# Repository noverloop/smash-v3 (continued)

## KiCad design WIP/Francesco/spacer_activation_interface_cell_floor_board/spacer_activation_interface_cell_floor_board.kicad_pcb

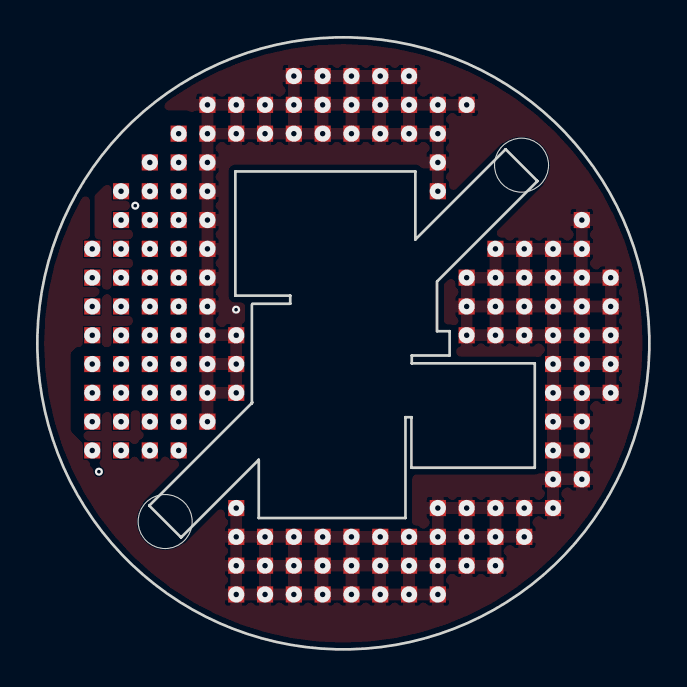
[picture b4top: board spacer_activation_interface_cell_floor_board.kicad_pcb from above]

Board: 4 copper layers, 34.0 x 34.0 mm, 4 parts (1 on the bottom side), 35 nets, no tracks yet.

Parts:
J_spacer_activation_interface_cell_floor_board_top: LGA_lands; J_spacer_activation_interface_cell_floor_board_top
MECH1, MECH2: smash_mech_potting
P_spacer_activation_interface_cell_floor_board_bot: LGA_lands; P_spacer_activation_interface_cell_floor_board_bot

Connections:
3V3: J_spacer_activation_interface_cell_floo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.1, J_spacer_activation_interface_cell_floo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.36, J_spacer_activation_interface_cell_floo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.41, P_spacer_activation_interface_cell_floo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.1, P_spacer_activation_interface_cell_floo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.36, P_spacer_activation_interface_cell_floo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.41
3V3_AON: J_spacer_activation_interface_cell_floo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.2, J_spacer_activation_interface_cell_floo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.37, P_spacer_activation_interface_cell_floo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.2, P_spacer_activation_interface_cell_floo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.37
ACTIVATE_CONFIRM: J_spacer_activation_interface_cell_floo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.3, P_spacer_activation_interface_cell_floo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.3
ACTIVATE_SET: J_spacer_activation_interface_cell_floo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.4, P_spacer_activation_interface_cell_floo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.4
BAT_PROT: J_spacer_activation_interface_cell_floo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.5, J_spacer_activation_interface_cell_floo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.38, P_spacer_activation_interface_cell_floo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.5, P_spacer_activation_interface_cell_floo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.38
BAT_RAW: J_spacer_activation_interface_cell_floo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.6, J_spacer_activation_interface_cell_floo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.39, P_spacer_activation_interface_cell_floo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.6, P_spacer_activation_interface_cell_floo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.39
BOOT0: J_spacer_activation_interface_cell_floo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.7, P_spacer_activation_interface_cell_floo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.7
COMP_5V: J_spacer_activation_interface_cell_floo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.8, J_spacer_activation_interface_cell_floo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.40, P_spacer_activation_interface_cell_floo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.8, P_spacer_activation_interface_cell_floo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.40
COMP_SWDCLK: J_spacer_activation_interface_cell_floo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.9, P_spacer_activation_interface_cell_floo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.9
COMP_SWDIO: J_spacer_activation_interface_cell_floo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.10, P_spacer_activation_interface_cell_floo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.10
EXT_CAN_RX: J_spacer_activation_interface_cell_floo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.11, P_spacer_activation_interface_cell_floo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.11
EXT_CAN_TX: J_spacer_activation_interface_cell_floo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.12, P_spacer_activation_interface_cell_floo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.12
FIN1_AOUT1: J_spacer_activation_interface_cell_floo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.13, P_spacer_activation_interface_cell_floo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.13
FIN2_AOUT1: J_spacer_activation_interface_cell_floo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.14, P_spacer_activation_interface_cell_floo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.14
FIN3_AOUT1: J_spacer_activation_interface_cell_floo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.15, P_spacer_activation_interface_cell_floo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.15
FIN4_AOUT1: J_spacer_activation_interface_cell_floo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.16, P_spacer_activation_interface_cell_floo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.16
FIN_HALL: J_spacer_activation_interface_cell_floo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.17, P_spacer_activation_interface_cell_floo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.17
FIN_VREF: J_spacer_activation_interface_cell_floo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.18, P_spacer_activation_interface_cell_floo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.18
FLEX_GND: J_spacer_activation_interface_cell_floo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.19, J_spacer_activation_interface_cell_floo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.42, J_spacer_activation_interface_cell_floo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.43, J_spacer_activation_interface_cell_floo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.44, J_spacer_activation_interface_cell_floo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.45, J_spacer_activation_interface_cell_floo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.46, J_spacer_activation_interface_cell_floo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.47, J_spacer_activation_interface_cell_floo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.48, J_spacer_activation_interface_cell_floo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.49, J_spacer_activation_interface_cell_floo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.50, J_spacer_activation_interface_cell_floo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.51, J_spacer_activation_interface_cell_floo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.52, J_spacer_activation_interface_cell_floo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.53, J_spacer_activation_interface_cell_floo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.54, J_spacer_activation_interface_cell_floo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.55, J_spacer_activation_interface_cell_floo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.56, J_spacer_activation_interface_cell_floo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.57, J_spacer_activation_interface_cell_floo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.58, J_spacer_activation_interface_cell_floo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.59, J_spacer_activation_interface_cell_floo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.60, J_spacer_activation_interface_cell_floo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.61, J_spacer_activation_interface_cell_floo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.62, J_spacer_activation_interface_cell_floo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.63, J_spacer_activation_interface_cell_floo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.64, J_spacer_activation_interface_cell_floo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.65, J_spacer_activation_interface_cell_floo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.66, J_spacer_activation_interface_cell_floo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.67, J_spacer_activation_interface_cell_floo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.68, J_spacer_activation_interface_cell_floo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.69, J_spacer_activation_interface_cell_floo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.70, J_spacer_activation_interface_cell_floo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.71, J_spacer_activation_interface_cell_floo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.72, J_spacer_activation_interface_cell_floo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.73, J_spacer_activation_interface_cell_floo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.74, J_spacer_activation_interface_cell_floo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.75, J_spacer_activation_interface_cell_floo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.76, J_spacer_activation_interface_cell_floo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.77, J_spacer_activation_interface_cell_floo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.78, J_spacer_activation_interface_cell_floo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.79, J_spacer_activation_interface_cell_floo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.80, J_spacer_activation_interface_cell_floo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.81, J_spacer_activation_interface_cell_floo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.82, J_spacer_activation_interface_cell_floo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.83, J_spacer_activation_interface_cell_floo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.84, J_spacer_activation_interface_cell_floo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.85, J_spacer_activation_interface_cell_floo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.86, J_spacer_activation_interface_cell_floo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.87, J_spacer_activation_interface_cell_floo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.88, J_spacer_activation_interface_cell_floo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.89, J_spacer_activation_interface_cell_floo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.90, J_spacer_activation_interface_cell_floo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.91, J_spacer_activation_interface_cell_floo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.92, J_spacer_activation_interface_cell_floo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.93, J_spacer_activation_interface_cell_floo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.94, J_spacer_activation_interface_cell_floo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.95, J_spacer_activation_interface_cell_floo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.96, J_spacer_activation_interface_cell_floo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.97, J_spacer_activation_interface_cell_floo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.98, J_spacer_activation_interface_cell_floo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.99, J_spacer_activation_interface_cell_floo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.100, J_spacer_activation_interface_cell_floo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.101, J_spacer_activation_interface_cell_floo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.102, J_spacer_activation_interface_cell_floo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.103, J_spacer_activation_interface_cell_floo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.104, J_spacer_activation_interface_cell_floo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.105, J_spacer_activation_interface_cell_floo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.106, J_spacer_activation_interface_cell_floo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.107, J_spacer_activation_interface_cell_floo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.108, J_spacer_activation_interface_cell_floo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.109, J_spacer_activation_interface_cell_floo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.110, J_spacer_activation_interface_cell_floo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.111, J_spacer_activation_interface_cell_floo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.112, J_spacer_activation_interface_cell_floo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.113, J_spacer_activation_interface_cell_floo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.114, J_spacer_activation_interface_cell_floo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.115, J_spacer_activation_interface_cell_floo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.116, J_spacer_activation_interface_cell_floo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.117, J_spacer_activation_interface_cell_floo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.118, J_spacer_activation_interface_cell_floo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.119, J_spacer_activation_interface_cell_floo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.120, J_spacer_activation_interface_cell_floo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.121, J_spacer_activation_interface_cell_floo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.122, J_spacer_activation_interface_cell_floo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.123, J_spacer_activation_interface_cell_floo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.124, J_spacer_activation_interface_cell_floo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.125, J_spacer_activation_interface_cell_floo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.126, J_spacer_activation_interface_cell_floo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.127, J_spacer_activation_interface_cell_floo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.128, J_spacer_activation_interface_cell_floo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.129, J_spacer_activation_interface_cell_floo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.130, J_spacer_activation_interface_cell_floo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.131, J_spacer_activation_interface_cell_floo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.132, J_spacer_activation_interface_cell_floo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.133, J_spacer_activation_interface_cell_floo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.134, J_spacer_activation_interface_cell_floo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.135, J_spacer_activation_interface_cell_floo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.136, J_spacer_activation_interface_cell_floo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.137, J_spacer_activation_interface_cell_floo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.138, J_spacer_activation_interface_cell_floo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.139, J_spacer_activation_interface_cell_floo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.140, J_spacer_activation_interface_cell_floo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.141, J_spacer_activation_interface_cell_floo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.142, J_spacer_activation_interface_cell_floo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.143, J_spacer_activation_interface_cell_floo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.144, J_spacer_activation_interface_cell_floo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.145, J_spacer_activation_interface_cell_floo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.146, J_spacer_activation_interface_cell_floo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.147, J_spacer_activation_interface_cell_floo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.148, J_spacer_activation_interface_cell_floo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.149, J_spacer_activation_interface_cell_floo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.150, P_spacer_activation_interface_cell_floo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.19, P_spacer_activation_interface_cell_floo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.42, P_spacer_activation_interface_cell_floo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.43, P_spacer_activation_interface_cell_floo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.44, P_spacer_activation_interface_cell_floo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.45, P_spacer_activation_interface_cell_floo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.46, P_spacer_activation_interface_cell_floo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.47, P_spacer_activation_interface_cell_floo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.48, P_spacer_activation_interface_cell_floo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.49, P_spacer_activation_interface_cell_floo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.50, P_spacer_activation_interface_cell_floo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.51, P_spacer_activation_interface_cell_floo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.52, P_spacer_activation_interface_cell_floo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.53, P_spacer_activation_interface_cell_floo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.54, P_spacer_activation_interface_cell_floo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.55, P_spacer_activation_interface_cell_floo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.56, P_spacer_activation_interface_cell_floo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.57, P_spacer_activation_interface_cell_floo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.58, P_spacer_activation_interface_cell_floo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.59, P_spacer_activation_interface_cell_floo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.60, P_spacer_activation_interface_cell_floo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.61, P_spacer_activation_interface_cell_floo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.62, P_spacer_activation_interface_cell_floo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.63, P_spacer_activation_interface_cell_floo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.64, P_spacer_activation_interface_cell_floo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.65, P_spacer_activation_interface_cell_floo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.66, P_spacer_activation_interface_cell_floo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.67, P_spacer_activation_interface_cell_floo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.68, P_spacer_activation_interface_cell_floo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.69, P_spacer_activation_interface_cell_floo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.70, P_spacer_activation_interface_cell_floo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.71, P_spacer_activation_interface_cell_floo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.72, P_spacer_activation_interface_cell_floo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.73, P_spacer_activation_interface_cell_floo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.74, P_spacer_activation_interface_cell_floo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.75, P_spacer_activation_interface_cell_floo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.76, P_spacer_activation_interface_cell_floo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.77, P_spacer_activation_interface_cell_floo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.78, P_spacer_activation_interface_cell_floo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.79, P_spacer_activation_interface_cell_floo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.80, P_spacer_activation_interface_cell_floo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.81, P_spacer_activation_interface_cell_floo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.82, P_spacer_activation_interface_cell_floo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.83, P_spacer_activation_interface_cell_floo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.84, P_spacer_activation_interface_cell_floo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.85, P_spacer_activation_interface_cell_floo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.86, P_spacer_activation_interface_cell_floo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.87, P_spacer_activation_interface_cell_floo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.88, P_spacer_activation_interface_cell_floo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.89, P_spacer_activation_interface_cell_floo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.90, P_spacer_activation_interface_cell_floo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.91, P_spacer_activation_interface_cell_floo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.92, P_spacer_activation_interface_cell_floo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.93, P_spacer_activation_interface_cell_floo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.94, P_spacer_activation_interface_cell_floo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.95, P_spacer_activation_interface_cell_floo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.96, P_spacer_activation_interface_cell_floo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.97, P_spacer_activation_interface_cell_floo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.98, P_spacer_activation_interface_cell_floo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.99, P_spacer_activation_interface_cell_floo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.100, P_spacer_activation_interface_cell_floo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.101, P_spacer_activation_interface_cell_floo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.102, P_spacer_activation_interface_cell_floo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.103, P_spacer_activation_interface_cell_floo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.104, P_spacer_activation_interface_cell_floo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.105, P_spacer_activation_interface_cell_floo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.106, P_spacer_activation_interface_cell_floo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.107, P_spacer_activation_interface_cell_floo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.108, P_spacer_activation_interface_cell_floo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.109, P_spacer_activation_interface_cell_floo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.110, P_spacer_activation_interface_cell_floo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.111, P_spacer_activation_interface_cell_floo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.112, P_spacer_activation_interface_cell_floo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.113, P_spacer_activation_interface_cell_floo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.114, P_spacer_activation_interface_cell_floo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.115, P_spacer_activation_interface_cell_floo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.116, P_spacer_activation_interface_cell_floo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.117, P_spacer_activation_interface_cell_floo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.118, P_spacer_activation_interface_cell_floo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.119, P_spacer_activation_interface_cell_floo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.120, P_spacer_activation_interface_cell_floo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.121, P_spacer_activation_interface_cell_floo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.122, P_spacer_activation_interface_cell_floo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.123, P_spacer_activation_interface_cell_floo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.124, P_spacer_activation_interface_cell_floo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.125, P_spacer_activation_interface_cell_floo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.126, P_spacer_activation_interface_cell_floo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.127, P_spacer_activation_interface_cell_floo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.128, P_spacer_activation_interface_cell_floo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.129, P_spacer_activation_interface_cell_floo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.130, P_spacer_activation_interface_cell_floo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.131, P_spacer_activation_interface_cell_floo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.132, P_spacer_activation_interface_cell_floo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.133, P_spacer_activation_interface_cell_floo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.134, P_spacer_activation_interface_cell_floo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.135, P_spacer_activation_interface_cell_floo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.136, P_spacer_activation_interface_cell_floo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.137, P_spacer_activation_interface_cell_floo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.138, P_spacer_activation_interface_cell_floo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.139, P_spacer_activation_interface_cell_floo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.140, P_spacer_activation_interface_cell_floo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.141, P_spacer_activation_interface_cell_floo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.142, P_spacer_activation_interface_cell_floo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.143, P_spacer_activation_interface_cell_floo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.144, P_spacer_activation_interface_cell_floo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.145, P_spacer_activation_interface_cell_floo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.146, P_spacer_activation_interface_cell_floo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.147, P_spacer_activation_interface_cell_floo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.148, P_spacer_activation_interface_cell_floo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.149, P_spacer_activation_interface_cell_floo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.150
GPIO_EXT_0: J_spacer_activation_interface_cell_floo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.20, P_spacer_activation_interface_cell_floo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.20
GPIO_EXT_1: J_spacer_activation_interface_cell_floo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.21, P_spacer_activation_interface_cell_floo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.21
GPIO_EXT_2: J_spacer_activation_interface_cell_floo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.22, P_spacer_activation_interface_cell_floo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.22
GPIO_EXT_3: J_spacer_activation_interface_cell_floo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.23, P_spacer_activation_interface_cell_floo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.23
H3LIS_INT1: J_spacer_activation_interface_cell_floo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.24, P_spacer_activation_interface_cell_floo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.24
I2C3_SCL: J_spacer_activation_interface_cell_floo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.25, P_spacer_activation_interface_cell_floo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.25
I2C3_SDA: J_spacer_activation_interface_cell_floo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.26, P_spacer_activation_interface_cell_floo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.26
JUMP_WAKE: J_spacer_activation_interface_cell_floo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.27, P_spacer_activation_interface_cell_floo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.27
NRST: J_spacer_activation_interface_cell_floo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.28, P_spacer_activation_interface_cell_floo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.28
SWO: J_spacer_activation_interface_cell_floo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.29, P_spacer_activation_interface_cell_floo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.29
SYS_I2C_SCL: J_spacer_activation_interface_cell_floo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.30, P_spacer_activation_interface_cell_floo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.30
SYS_I2C_SDA: J_spacer_activation_interface_cell_floo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.31, P_spacer_activation_interface_cell_floo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.31
SYS_SPI_CS_FIN: J_spacer_activation_interface_cell_floo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.32, P_spacer_activation_interface_cell_floo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.32
SYS_SPI_MISO: J_spacer_activation_interface_cell_floo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.33, P_spacer_activation_interface_cell_floo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.33
SYS_SPI_MOSI: J_spacer_activation_interface_cell_floo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.34, P_spacer_activation_interface_cell_floo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.34
SYS_SPI_SCLK: J_spacer_activation_interface_cell_floo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.35, P_spacer_activation_interface_cell_floo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.35

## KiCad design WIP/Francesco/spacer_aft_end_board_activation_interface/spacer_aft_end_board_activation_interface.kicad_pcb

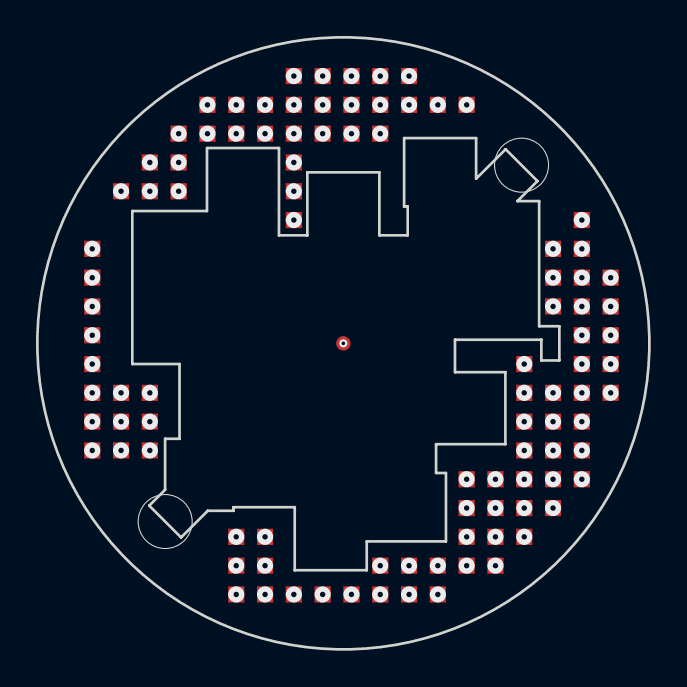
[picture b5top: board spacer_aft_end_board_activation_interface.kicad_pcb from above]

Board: 4 copper layers, 34.0 x 34.0 mm, 5 parts (1 on the bottom side), 33 nets, no tracks yet.

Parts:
J_spacer_aft_end_board_activation_interface_top: LGA_lands; J_spacer_aft_end_board_activation_interface_top
MECH1, MECH2: smash_mech_potting
P_spacer_aft_end_board_activation_interface_bot: LGA_lands; P_spacer_aft_end_board_activation_interface_bot
SP_aft_end_board_activation_interface: SP_aft_end_board_activation_interface; Spacer_Mechanical_34mm

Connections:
3V3: J_spacer_aft_end_board_activation_inter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.1, J_spacer_aft_end_board_activation_inter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.34, J_spacer_aft_end_board_activation_inter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.40, P_spacer_aft_end_board_activation_inter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.1, P_spacer_aft_end_board_activation_inter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.34, P_spacer_aft_end_board_activation_inter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.40
3V3_AON: J_spacer_aft_end_board_activation_inter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.2, J_spacer_aft_end_board_activation_inter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.35, P_spacer_aft_end_board_activation_inter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.2, P_spacer_aft_end_board_activation_inter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.35
ACTIVATE_CONFIRM: J_spacer_aft_end_board_activation_inter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.3, P_spacer_aft_end_board_activation_inter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.3
ACTIVATE_SET: J_spacer_aft_end_board_activation_inter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.4, P_spacer_aft_end_board_activation_inter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.4
BAT_PROT: J_spacer_aft_end_board_activation_inter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.5, J_spacer_aft_end_board_activation_inter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.36, P_spacer_aft_end_board_activation_inter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.5, P_spacer_aft_end_board_activation_inter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.36
BAT_RAW: J_spacer_aft_end_board_activation_inter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.6, J_spacer_aft_end_board_activation_inter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.37, P_spacer_aft_end_board_activation_inter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.6, P_spacer_aft_end_board_activation_inter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.37
BOOT0: J_spacer_aft_end_board_activation_inter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.7, P_spacer_aft_end_board_activation_inter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.7
COMP_5V: J_spacer_aft_end_board_activation_inter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.8, J_spacer_aft_end_board_activation_inter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.38, P_spacer_aft_end_board_activation_inter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.8, P_spacer_aft_end_board_activation_inter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.38
COMP_SWDCLK: J_spacer_aft_end_board_activation_inter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.9, P_spacer_aft_end_board_activation_inter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.9
COMP_SWDIO: J_spacer_aft_end_board_activation_inter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.10, P_spacer_aft_end_board_activation_inter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.10
EXT_CAN_RX: J_spacer_aft_end_board_activation_inter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.11, P_spacer_aft_end_board_activation_inter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.11
EXT_CAN_TX: J_spacer_aft_end_board_activation_inter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.12, P_spacer_aft_end_board_activation_inter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.12
FIN1_AOUT1: J_spacer_aft_end_board_activation_inter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.13, P_spacer_aft_end_board_activation_inter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.13
FIN2_AOUT1: J_spacer_aft_end_board_activation_inter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.14, P_spacer_aft_end_board_activation_inter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.14
FIN3_AOUT1: J_spacer_aft_end_board_activation_inter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.15, P_spacer_aft_end_board_activation_inter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.15
FIN4_AOUT1: J_spacer_aft_end_board_activation_inter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.16, P_spacer_aft_end_board_activation_inter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.16
FIN_HALL: J_spacer_aft_end_board_activation_inter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.17, P_spacer_aft_end_board_activation_inter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.17
FIN_VREF: J_spacer_aft_end_board_activation_inter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.18, P_spacer_aft_end_board_activation_inter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.18
FIRE_HV: J_spacer_aft_end_board_activation_inter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.19, J_spacer_aft_end_board_activation_inter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.39, P_spacer_aft_end_board_activation_inter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.19, P_spacer_aft_end_board_activation_inter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.39
FLEX_GND: J_spacer_aft_end_board_activation_inter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.20, J_spacer_aft_end_board_activation_inter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.41, J_spacer_aft_end_board_activation_inter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.42, J_spacer_aft_end_board_activation_inter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.43, J_spacer_aft_end_board_activation_inter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.44, J_spacer_aft_end_board_activation_inter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.45, J_spacer_aft_end_board_activation_inter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.46, J_spacer_aft_end_board_activation_inter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.47, J_spacer_aft_end_board_activation_inter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.48, J_spacer_aft_end_board_activation_inter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.49, J_spacer_aft_end_board_activation_inter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.50, J_spacer_aft_end_board_activation_inter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.51, J_spacer_aft_end_board_activation_inter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.52, J_spacer_aft_end_board_activation_inter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.53, J_spacer_aft_end_board_activation_inter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.54, J_spacer_aft_end_board_activation_inter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.55, J_spacer_aft_end_board_activation_inter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.56, J_spacer_aft_end_board_activation_inter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.57, J_spacer_aft_end_board_activation_inter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.58, J_spacer_aft_end_board_activation_inter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.59, J_spacer_aft_end_board_activation_inter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.60, J_spacer_aft_end_board_activation_inter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.61, J_spacer_aft_end_board_activation_inter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.62, J_spacer_aft_end_board_activation_inter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.63, J_spacer_aft_end_board_activation_inter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.64, J_spacer_aft_end_board_activation_inter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.65, J_spacer_aft_end_board_activation_inter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.66, J_spacer_aft_end_board_activation_inter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.67, J_spacer_aft_end_board_activation_inter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.68, J_spacer_aft_end_board_activation_inter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.69, J_spacer_aft_end_board_activation_inter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.70, J_spacer_aft_end_board_activation_inter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.71, J_spacer_aft_end_board_activation_inter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.72, J_spacer_aft_end_board_activation_inter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.73, J_spacer_aft_end_board_activation_inter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.74, J_spacer_aft_end_board_activation_inter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.75, J_spacer_aft_end_board_activation_inter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.76, J_spacer_aft_end_board_activation_inter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.77, J_spacer_aft_end_board_activation_inter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.78, J_spacer_aft_end_board_activation_inter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.79, J_spacer_aft_end_board_activation_inter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.80, J_spacer_aft_end_board_activation_inter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.81, J_spacer_aft_end_board_activation_inter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.82, J_spacer_aft_end_board_activation_inter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.83, J_spacer_aft_end_board_activation_inter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.84, J_spacer_aft_end_board_activation_inter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.85, J_spacer_aft_end_board_activation_inter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.86, J_spacer_aft_end_board_activation_inter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.87, J_spacer_aft_end_board_activation_inter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.88, J_spacer_aft_end_board_activation_inter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.89, J_spacer_aft_end_board_activation_inter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.90, J_spacer_aft_end_board_activation_inter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.91, J_spacer_aft_end_board_activation_inter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.92, J_spacer_aft_end_board_activation_inter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.93, J_spacer_aft_end_board_activation_inter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.94, J_spacer_aft_end_board_activation_inter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.95, J_spacer_aft_end_board_activation_inter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.96, J_spacer_aft_end_board_activation_inter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.97, J_spacer_aft_end_board_activation_inter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.98, P_spacer_aft_end_board_activation_inter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.20, P_spacer_aft_end_board_activation_inter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.41, P_spacer_aft_end_board_activation_inter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.42, P_spacer_aft_end_board_activation_inter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.43, P_spacer_aft_end_board_activation_inter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.44, P_spacer_aft_end_board_activation_inter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.45, P_spacer_aft_end_board_activation_inter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.46, P_spacer_aft_end_board_activation_inter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.47, P_spacer_aft_end_board_activation_inter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.48, P_spacer_aft_end_board_activation_inter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.49, P_spacer_aft_end_board_activation_inter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.50, P_spacer_aft_end_board_activation_inter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.51, P_spacer_aft_end_board_activation_inter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.52, P_spacer_aft_end_board_activation_inter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.53, P_spacer_aft_end_board_activation_inter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.54, P_spacer_aft_end_board_activation_inter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.55, P_spacer_aft_end_board_activation_inter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.56, P_spacer_aft_end_board_activation_inter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.57, P_spacer_aft_end_board_activation_inter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.58, P_spacer_aft_end_board_activation_inter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.59, P_spacer_aft_end_board_activation_inter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.60, P_spacer_aft_end_board_activation_inter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.61, P_spacer_aft_end_board_activation_inter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.62, P_spacer_aft_end_board_activation_inter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.63, P_spacer_aft_end_board_activation_inter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.64, P_spacer_aft_end_board_activation_inter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.65, P_spacer_aft_end_board_activation_inter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.66, P_spacer_aft_end_board_activation_inter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.67, P_spacer_aft_end_board_activation_inter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.68, P_spacer_aft_end_board_activation_inter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.69, P_spacer_aft_end_board_activation_inter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.70, P_spacer_aft_end_board_activation_inter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.71, P_spacer_aft_end_board_activation_inter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.72, P_spacer_aft_end_board_activation_inter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.73, P_spacer_aft_end_board_activation_inter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.74, P_spacer_aft_end_board_activation_inter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.75, P_spacer_aft_end_board_activation_inter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.76, P_spacer_aft_end_board_activation_inter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.77, P_spacer_aft_end_board_activation_inter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.78, P_spacer_aft_end_board_activation_inter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.79, P_spacer_aft_end_board_activation_inter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.80, P_spacer_aft_end_board_activation_inter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.81, P_spacer_aft_end_board_activation_inter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.82, P_spacer_aft_end_board_activation_inter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.83, P_spacer_aft_end_board_activation_inter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.84, P_spacer_aft_end_board_activation_inter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.85, P_spacer_aft_end_board_activation_inter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.86, P_spacer_aft_end_board_activation_inter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.87, P_spacer_aft_end_board_activation_inter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.88, P_spacer_aft_end_board_activation_inter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.89, P_spacer_aft_end_board_activation_inter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.90, P_spacer_aft_end_board_activation_inter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.91, P_spacer_aft_end_board_activation_inter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.92, P_spacer_aft_end_board_activation_inter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.93, P_spacer_aft_end_board_activation_inter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.94, P_spacer_aft_end_board_activation_inter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.95, P_spacer_aft_end_board_activation_inter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.96, P_spacer_aft_end_board_activation_inter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.97, P_spacer_aft_end_board_activation_inter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.98, SP_aft_end_board_activation_interface.1
GPIO_EXT_0: J_spacer_aft_end_board_activation_inter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.21, P_spacer_aft_end_board_activation_inter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.21
GPIO_EXT_1: J_spacer_aft_end_board_activation_inter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.22, P_spacer_aft_end_board_activation_inter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.22
GPIO_EXT_2: J_spacer_aft_end_board_activation_inter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.23, P_spacer_aft_end_board_activation_inter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.23
GPIO_EXT_3: J_spacer_aft_end_board_activation_inter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.24, P_spacer_aft_end_board_activation_inter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.24
JUMP_WAKE: J_spacer_aft_end_board_activation_inter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.25, P_spacer_aft_end_board_activation_inter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.25
NRST: J_spacer_aft_end_board_activation_inter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.26, P_spacer_aft_end_board_activation_inter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.26
SWO: J_spacer_aft_end_board_activation_inter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.27, P_spacer_aft_end_board_activation_inter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.27
SYS_I2C_SCL: J_spacer_aft_end_board_activation_inter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.28, P_spacer_aft_end_board_activation_inter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.28
SYS_I2C_SDA: J_spacer_aft_end_board_activation_inter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.29, P_spacer_aft_end_board_activation_inter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.29
SYS_SPI_CS_FIN: J_spacer_aft_end_board_activation_inter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.30, P_spacer_aft_end_board_activation_inter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.30
SYS_SPI_MISO: J_spacer_aft_end_board_activation_inter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.31, P_spacer_aft_end_board_activation_inter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.31
SYS_SPI_MOSI: J_spacer_aft_end_board_activation_inter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.32, P_spacer_aft_end_board_activation_inter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.32
SYS_SPI_SCLK: J_spacer_aft_end_board_activation_inter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.33, P_spacer_aft_end_board_activation_inter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.33

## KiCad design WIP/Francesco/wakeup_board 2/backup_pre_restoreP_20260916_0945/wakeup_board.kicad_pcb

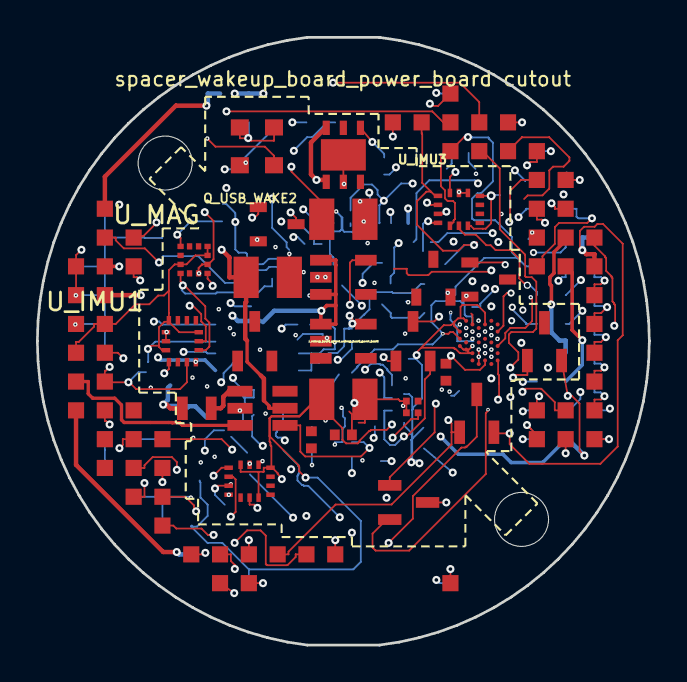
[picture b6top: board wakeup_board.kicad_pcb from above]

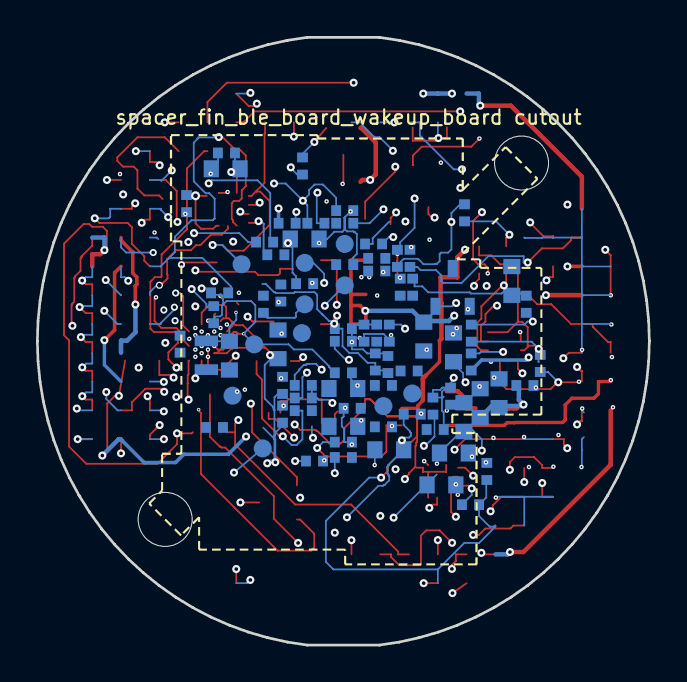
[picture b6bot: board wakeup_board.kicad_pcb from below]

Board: 14 copper layers, 34.0 x 33.8 mm, 111 parts (84 on the bottom side), 63 nets.

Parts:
CBOOST_IN1_1, CBOOST_IN1_2, CBOOST_IN1_3, CBOOST_IN1_4, CBOOST_IN1_5: C-Series MIL-PRF-32535 X7R 0603 2.2uF; Capacitor_SMD_C_0603_1608Metric
CBOOST_IN2: C0402 X7R 100nF; Capacitor_SMD_C_0402_1005Metric
CBOOST_OUT1: T491T 22uF (3528-12 thinnest variant); Capacitor_Tantalum_SMD_CP_EIA-3528-12_Kemet-T
CBOOST_OUT2: C0402 X7R 100nF; Capacitor_SMD_C_0402_1005Metric
CMAIN_HOLD: C0402 X7R 100nF; Capacitor_SMD_C_0402_1005Metric
COUT1, COUT2: T491T 22uF (3528-12 thinnest variant); Capacitor_Tantalum_SMD_CP_EIA-3528-12_Kemet-T
COUT3: C0402 X7R 100nF; Capacitor_SMD_C_0402_1005Metric
C_AON_IN: C-Series MIL-PRF-32535 X7R 0603 1uF; Capacitor_SMD_C_0603_1608Metric
C_AON_OUT: C-Series MIL-PRF-32535 X7R 0603 1uF; Capacitor_SMD_C_0603_1608Metric
C_CAM_VDD: C0402 X7R 100nF; Capacitor_SMD_C_0402_1005Metric
C_IMU1_1, C_IMU2_1, C_IMU3_1: C0402 X7R 100nF; Capacitor_SMD_C_0402_1005Metric
C_IMU1_2, C_IMU2_2, C_IMU3_2: C-Series MIL-PRF-32535 X7R 0603 2.2uF; Capacitor_SMD_C_0603_1608Metric
C_IMU1_3, C_IMU2_3, C_IMU3_3: C0402 X7R 10nF; Capacitor_SMD_C_0402_1005Metric
C_IR_WAKE: C0402 X7R 10nF; Capacitor_SMD_C_0402_1005Metric
C_MAG1: C0402 X7R 100nF; Capacitor_SMD_C_0402_1005Metric
C_MAG2: C-Series MIL-PRF-32535 X7R 0603 1uF; Capacitor_SMD_C_0603_1608Metric
C_MAG_C1: C-Series MIL-PRF-32535 X7R 0402 220nF; Capacitor_SMD_C_0402_1005Metric
C_MAG_SHELF: C0402 X7R 100nF; Capacitor_SMD_C_0402_1005Metric
C_MAG_WAKE: C0402 X7R 100nF; Capacitor_SMD_C_0402_1005Metric
C_TMR_LDO: C-Series MIL-PRF-32535 X7R 0603 1uF; Capacitor_SMD_C_0603_1608Metric
C_WBA_BULK_1, C_WBA_BULK_2: C-Series MIL-PRF-32535 X7R 0603 2.2uF; Capacitor_SMD_C_0603_1608Metric
C_WBA_HSE_VDD: C0402 X7R 100nF; Capacitor_SMD_C_0402_1005Metric
C_WBA_NRST: C0402 X7R 100nF; Capacitor_SMD_C_0402_1005Metric
C_WBA_PI1, C_WBA_PI2: SQCSVA 0.5pF; Capacitor_SMD_C_0402_1005Metric
C_WBA_VDD1, C_WBA_VDD2: C0402 X7R 100nF; Capacitor_SMD_C_0402_1005Metric
C_WBA_VDD11: C-Series MIL-PRF-32535 X7R 0603 2.2uF; Capacitor_SMD_C_0603_1608Metric
C_WBA_VDDA: C0402 X7R 100nF; Capacitor_SMD_C_0402_1005Metric
C_WBA_VDDANA: C0402 X7R 100nF; Capacitor_SMD_C_0402_1005Metric
C_WBA_VDDHPA: C0402 X7R 100nF; Capacitor_SMD_C_0402_1005Metric
C_WBA_VDDRF: C0402 X7R 100nF; Capacitor_SMD_C_0402_1005Metric
C_WBA_VDDRFPA: C0402 X7R 100nF; Capacitor_SMD_C_0402_1005Metric
C_WBA_VDDSMPS: C0402 X7R 100nF; Capacitor_SMD_C_0402_1005Metric
D_AON_WAKE: BAT64-06-TP; SOT95P237X125-3N
D_JUMP_WAKE: BAT64-06-TP; SOT95P237X125-3N
J_wakeup_board_spacer_wakeup_board_power_board: LGA_lands; J_wakeup_board_spacer_wakeup_board_power_board
L_PWR: TMS201210ALM-2R2MTAA; Inductor_SMD_L_2012_2.0x1.25mm
L_WBA_PI: WE-KI 0402 2.7nH (74479xxxxx family); Inductor_SMD_L_0402_1005Metric
L_WBA_SMPS: TMS201210ALM-2R2MTAA; Inductor_SMD_L_2012_2.0x1.25mm
QHOLD, QHOLD2: BSS138LT1G; SOT96P237X111-3N
QMAIN: IRLML6402TRPBF; SOT95P237X112-3N
Q_AON_EN: IRLML6402TRPBF; SOT95P237X112-3N
Q_USB_WAKE2: BSS138LT1G; SOT96P237X111-3N
Q_WBA_RST: BSS138LT1G; SOT96P237X111-3N
RAON_PU: CRCW0402 1M 1% e3; Resistor_SMD_R_0402_1005Metric
RHOLD2_G: CRCW0402 100 1% e3; Resistor_SMD_R_0402_1005Metric
RHOLD2_PD: CRCW0402 100k 1% e3; Resistor_SMD_R_0402_1005Metric
RHOLD_AON: CRCW0402 1k 1% e3; Resistor_SMD_R_0402_1005Metric
RHOLD_G: CRCW0402 100 1% e3; Resistor_SMD_R_0402_1005Metric
RHOLD_PD: CRCW0402 100k 1% e3; Resistor_SMD_R_0402_1005Metric
RMAIN_PU: CRCW0402 1M 1% e3; Resistor_SMD_R_0402_1005Metric
RPU_I2C2_SCL, RPU_I2C2_SDA, RPU_I2C3_SCL, RPU_I2C3_SDA: CRCW0402 4.7k 1% e3; Resistor_SMD_R_0402_1005Metric
RPU_IR_WAKE: CRCW0402 470k 1% e3; Resistor_SMD_R_0402_1005Metric
RPU_MAG_WAKE: CRCW0402 1M 1% e3; Resistor_SMD_R_0402_1005Metric
RPU_SCL_EXT: CRCW0402 4.7k 1% e3; Resistor_SMD_R_0402_1005Metric
RPU_SDA_EXT: CRCW0402 4.7k 1% e3; Resistor_SMD_R_0402_1005Metric
R_BOOST_FB1: CRCW0402 220k 1% e3; Resistor_SMD_R_0402_1005Metric
R_BOOST_FB2: CRCW0402 100k 1% e3; Resistor_SMD_R_0402_1005Metric
R_IMU1_SCX_PU, R_IMU1_SDX_PU, R_IMU2_SCX_PU, R_IMU2_SDX_PU, R_IMU3_SCX_PU, R_IMU3_SDX_PU: CRCW0402 10k 1% e3; Resistor_SMD_R_0402_1005Metric
R_JUMP_PU: CRCW0402 22k 1% e3; Resistor_SMD_R_0402_1005Metric
R_JUMP_WAKE: CRCW0402 3.3k 1% e3; Resistor_SMD_R_0402_1005Metric
R_MAG_SHELF: CRCW0402 3.3k 1% e3; Resistor_SMD_R_0402_1005Metric
R_WBARST_PD: CRCW0402 100k 1% e3; Resistor_SMD_R_0402_1005Metric
R_WBA_BOOT0: CRCW0402 10k 1% e3; Resistor_SMD_R_0402_1005Metric
R_WBA_NRST: CRCW0402 10k 1% e3; Resistor_SMD_R_0402_1005Metric
R_WILK_ISO: CRCW0402 100 1% e3; Resistor_SMD_R_0402_1005Metric
TP_3V3: TP_3V3; TestPoint_TestPoint_Pad_D1.5mm
TP_BAT: TP_BAT; TestPoint_TestPoint_Pad_D1.5mm
TP_GND: TP_GND; TestPoint_TestPoint_Pad_D1.5mm
TP_IMU1_INT: TP_IMU1_INT; TestPoint_TestPoint_Pad_D1.5mm
TP_IMU2_INT: TP_IMU2_INT; TestPoint_TestPoint_Pad_D1.5mm
TP_IMU3_INT: TP_IMU3_INT; TestPoint_TestPoint_Pad_D1.5mm
TP_MAG_DRDY: TP_MAG_DRDY; TestPoint_TestPoint_Pad_D1.5mm
TP_WILK_A: TP_WILK_A; TestPoint_TestPoint_Pad_D1.5mm
TP_WILK_B: TP_WILK_B; TestPoint_TestPoint_Pad_D1.5mm
TP_YAGI_RF_A: TP_YAGI_RF_A; TestPoint_TestPoint_Pad_D1.5mm
TP_YAGI_RF_B: TP_YAGI_RF_B; TestPoint_TestPoint_Pad_D1.5mm
U_AON_LDO: TPS7A0233PDBVR; SOT95P280X145-5N
U_BOOST: MCP1640CT-I/CHY; SOT95P270X145-6N
U_IMU1, U_IMU2, U_IMU3: ISM330DHCXTR; LSM6DS3USTR (LGA-14)
U_MAG: IIS2MDCTR
U_MAG_SHELF: RR123-1H02-612
U_MAG_WAKE: SOT95P237X112-3N
U_PWR: LDL112PV33R; SON95P300X300X100-7N-D
U_TMR_LDO: TPS7A0233PDBVR; SOT95P280X145-5N
U_WBA: STM32WBA55HGF6TR; BGA41C35P13X7_298X276X50
Y_WBA_HSE: DSC1001CI5-032.0000; DSC1001CI50080000

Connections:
3V3: COUT1.1, COUT2.1, COUT3.1, C_IMU1_1.1, C_IMU1_2.1, C_IMU1_3.1, C_IMU2_1.1, C_IMU2_2.1, C_IMU2_3.1, C_IMU3_1.1, C_IMU3_2.1, C_IMU3_3.1, C_MAG1.1, C_MAG2.1, J_wakeup_board_spacer_wakeup_board_powe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.1, J_wakeup_board_spacer_wakeup_board_powe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.55, J_wakeup_board_spacer_wakeup_board_powe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.62, RPU_I2C2_SCL.1, RPU_I2C2_SDA.1, RPU_I2C3_SCL.1, RPU_I2C3_SDA.1, RPU_SCL_EXT.1, RPU_SDA_EXT.1, R_IMU1_SCX_PU.1, R_IMU1_SDX_PU.1, R_IMU2_SCX_PU.1, R_IMU2_SDX_PU.1, R_IMU3_SCX_PU.1, R_IMU3_SDX_PU.1, TP_3V3.1, U_IMU1.5, U_IMU1.8, U_IMU1.12, U_IMU2.5, U_IMU2.8, U_IMU2.12, U_IMU3.1, U_IMU3.5, U_IMU3.8, U_IMU3.12, U_MAG.3, U_MAG.9, U_MAG.10, U_PWR.4
3V3_AON: C_AON_OUT.1, C_MAG_WAKE.1, C_WBA_BULK_1.1, C_WBA_BULK_2.1, C_WBA_HSE_VDD.1, C_WBA_VDD1.1, C_WBA_VDD2.1, C_WBA_VDDA.1, C_WBA_VDDANA.1, C_WBA_VDDHPA.1, C_WBA_VDDRF.1, C_WBA_VDDRFPA.1, C_WBA_VDDSMPS.1, RPU_IR_WAKE.1, RPU_MAG_WAKE.1, R_WBA_NRST.1, U_AON_LDO.5, U_MAG_WAKE.1, U_WBA.A6, U_WBA.A10, U_WBA.B5, U_WBA.B13, U_WBA.C4, U_WBA.C6, U_WBA.E12, U_WBA.G4, Y_WBA_HSE.1, Y_WBA_HSE.4
AON_EN: Q_AON_EN.3, RHOLD_AON.2, U_AON_LDO.3
AON_EN_GATE: D_AON_WAKE.3, Q_AON_EN.1, Q_USB_WAKE2.3, RAON_PU.2
BAT_PROT: J_wakeup_board_spacer_wakeup_board_powe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.7, J_wakeup_board_spacer_wakeup_board_powe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.56, QMAIN.2, TP_BAT.1
BAT_RAW: C_AON_IN.1, J_wakeup_board_spacer_wakeup_board_powe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.8, J_wakeup_board_spacer_wakeup_board_powe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.57, Q_AON_EN.2, RAON_PU.1, RMAIN_PU.1, R_JUMP_PU.1, U_AON_LDO.1, U_TMR_LDO.1, U_TMR_LDO.3
BOOST_FB: R_BOOST_FB1.2, R_BOOST_FB2.1, U_BOOST.4
BOOST_OUT: CBOOST_OUT1.1, CBOOST_OUT2.1, R_BOOST_FB1.1, U_BOOST.5, U_PWR.1, U_PWR.6
BOOST_SW: L_PWR.2, U_BOOST.1
COMP_1V8: C_CAM_VDD.1, J_wakeup_board_spacer_wakeup_board_powe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.10, J_wakeup_board_spacer_wakeup_board_powe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.58
COMP_5V: J_wakeup_board_spacer_wakeup_board_powe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.11, J_wakeup_board_spacer_wakeup_board_powe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.59
COMP_5V_RAW: J_wakeup_board_spacer_wakeup_board_powe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.12, J_wakeup_board_spacer_wakeup_board_powe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.60
FLEX_GND: CBOOST_IN1_1.2, CBOOST_IN1_2.2, CBOOST_IN1_3.2, CBOOST_IN1_4.2, CBOOST_IN1_5.2, CBOOST_IN2.2, CBOOST_OUT1.2, CBOOST_OUT2.2, CMAIN_HOLD.2, COUT1.2, COUT2.2, COUT3.2, C_AON_IN.2, C_AON_OUT.2, C_CAM_VDD.2, C_IMU1_1.2, C_IMU1_2.2, C_IMU1_3.2, C_IMU2_1.2, C_IMU2_2.2, C_IMU2_3.2, C_IMU3_1.2, C_IMU3_2.2, C_IMU3_3.2, C_IR_WAKE.2, C_MAG1.2, C_MAG2.2, C_MAG_C1.2, C_MAG_SHELF.2, C_MAG_WAKE.2, C_TMR_LDO.2, C_WBA_BULK_1.2, C_WBA_BULK_2.2, C_WBA_HSE_VDD.2, C_WBA_NRST.2, C_WBA_PI1.2, C_WBA_PI2.2, C_WBA_VDD1.2, C_WBA_VDD2.2, C_WBA_VDD11.2, C_WBA_VDDA.2, C_WBA_VDDANA.2, C_WBA_VDDHPA.2, C_WBA_VDDRF.2, C_WBA_VDDRFPA.2, C_WBA_VDDSMPS.2, J_wakeup_board_spacer_wakeup_board_powe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.18, J_wakeup_board_spacer_wakeup_board_powe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.63, J_wakeup_board_spacer_wakeup_board_powe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.64, J_wakeup_board_spacer_wakeup_board_powe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.65, QHOLD.2, QHOLD2.2, Q_USB_WAKE2.2, Q_WBA_RST.2, RHOLD2_PD.2, RHOLD_PD.2, R_BOOST_FB2.2, R_WBARST_PD.2, R_WBA_BOOT0.2, TP_GND.1, U_AON_LDO.2, U_BOOST.2, U_IMU1.1, U_IMU1.6, U_IMU1.7, U_IMU2.1, U_IMU2.6, U_IMU2.7, U_IMU3.6, U_IMU3.7, U_MAG.6, U_MAG.8, U_MAG_SHELF.1, U_MAG_SHELF.4, U_MAG_WAKE.3, U_PWR.2, U_PWR.7, U_TMR_LDO.2, U_WBA.A12, U_WBA.B9, U_WBA.D1, U_WBA.D3, U_WBA.D5, U_WBA.D13, U_WBA.G6, Y_WBA_HSE.2
I2C2_SCL: J_wakeup_board_spacer_wakeup_board_powe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.24, RPU_I2C2_SCL.2, U_IMU1.13, U_MAG.1, U_WBA.F3
I2C2_SDA: J_wakeup_board_spacer_wakeup_board_powe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.25, RPU_I2C2_SDA.2, U_IMU1.14, U_MAG.4, U_WBA.G2
I2C3_SCL: J_wakeup_board_spacer_wakeup_board_powe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.26, RPU_I2C3_SCL.2, U_IMU2.13, U_IMU3.13
I2C3_SDA: J_wakeup_board_spacer_wakeup_board_powe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.27, RPU_I2C3_SDA.2, U_IMU2.14, U_IMU3.14
IMU1_INT: J_wakeup_board_spacer_wakeup_board_powe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.28, TP_IMU1_INT.1, U_IMU1.4
IMU1_SCX: R_IMU1_SCX_PU.2, U_IMU1.3
IMU1_SDX: R_IMU1_SDX_PU.2, U_IMU1.2
IMU2_INT: J_wakeup_board_spacer_wakeup_board_powe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.29, TP_IMU2_INT.1, U_IMU2.4
IMU2_SCX: R_IMU2_SCX_PU.2, U_IMU2.3
IMU2_SDX: R_IMU2_SDX_PU.2, U_IMU2.2
IMU3_INT: J_wakeup_board_spacer_wakeup_board_powe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.30, TP_IMU3_INT.1, U_IMU3.4
IMU3_SCX: R_IMU3_SCX_PU.2, U_IMU3.3
IMU3_SDX: R_IMU3_SDX_PU.2, U_IMU3.2
IR_TX: J_wakeup_board_spacer_wakeup_board_powe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.31, U_WBA.D9
IR_WAKE: C_IR_WAKE.1, J_wakeup_board_spacer_wakeup_board_powe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.32, RPU_IR_WAKE.2, U_WBA.E6
JUMP_WAKE: R_JUMP_PU.2, R_JUMP_WAKE.2
JUMP_WAKE_K: D_AON_WAKE.1, D_JUMP_WAKE.1, R_JUMP_WAKE.1
MAG_C1_TERM: C_MAG_C1.1, U_MAG.5
MAG_DRDY: J_wakeup_board_spacer_wakeup_board_powe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.33, TP_MAG_DRDY.1, U_MAG.7
MAG_SHELF_K: D_AON_WAKE.2, D_JUMP_WAKE.2, R_MAG_SHELF.1
MAG_SHELF_N: R_MAG_SHELF.2, U_MAG_SHELF.3
MAG_WAKE_N: RPU_MAG_WAKE.2, U_MAG_WAKE.2, U_WBA.G8
MAIN_SW_GATE: CMAIN_HOLD.1, D_JUMP_WAKE.3, J_wakeup_board_spacer_wakeup_board_powe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.34, QHOLD.3, QHOLD2.3, QMAIN.1, RMAIN_PU.2
PWR_HOLD: J_wakeup_board_spacer_wakeup_board_powe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.36, RHOLD_G.1
QHOLD2_GATE: QHOLD2.1, RHOLD2_G.2, RHOLD2_PD.1
QHOLD_GATE: QHOLD.1, RHOLD_G.2, RHOLD_PD.1
REG_IN_MAIN: CBOOST_IN1_1.1, CBOOST_IN1_2.1, CBOOST_IN1_3.1, CBOOST_IN1_4.1, CBOOST_IN1_5.1, CBOOST_IN2.1, J_wakeup_board_spacer_wakeup_board_powe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.37, J_wakeup_board_spacer_wakeup_board_powe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.61, L_PWR.1, QMAIN.3, U_BOOST.3, U_BOOST.6
SYS_I2C_SCL: J_wakeup_board_spacer_wakeup_board_powe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.39, RPU_SCL_EXT.2
SYS_I2C_SDA: J_wakeup_board_spacer_wakeup_board_powe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.40, RPU_SDA_EXT.2
TMR_VDD: C_MAG_SHELF.1, C_TMR_LDO.1, U_MAG_SHELF.2, U_TMR_LDO.5
USBWK_GATE: J_wakeup_board_spacer_wakeup_board_powe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.45, Q_USB_WAKE2.1
WBA_AON_HOLD: RHOLD_AON.1, U_WBA.E4
WBA_BOOT0: J_wakeup_board_spacer_wakeup_board_powe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.46, R_WBA_BOOT0.1, U_WBA.C8
WBA_HCI_IRQ: J_wakeup_board_spacer_wakeup_board_powe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.47, U_WBA.C10
WBA_HCI_MISO: J_wakeup_board_spacer_wakeup_board_powe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.48, U_WBA.F9
WBA_HCI_MOSI: J_wakeup_board_spacer_wakeup_board_powe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.49, U_WBA.G10
WBA_HCI_NSS: J_wakeup_board_spacer_wakeup_board_powe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.50, U_WBA.F13
WBA_HCI_SCK: J_wakeup_board_spacer_wakeup_board_powe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.51, U_WBA.G12
WBA_HSE_IN: U_WBA.A8, Y_WBA_HSE.3
WBA_NRST: C_WBA_NRST.1, Q_WBA_RST.3, R_WBA_NRST.2, U_WBA.E2
WBA_RF: C_WBA_PI1.1, L_WBA_PI.1, U_WBA.C2
WBA_RF_M: C_WBA_PI2.1, L_WBA_PI.2
WBA_RST_CMD: J_wakeup_board_spacer_wakeup_board_powe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.52, Q_WBA_RST.1, R_WBARST_PD.1
WBA_UART_RX: J_wakeup_board_spacer_wakeup_board_powe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.53, U_WBA.E10
WBA_UART_TX: J_wakeup_board_spacer_wakeup_board_powe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.54, U_WBA.F11
WBA_VDD11: C_WBA_VDD11.1, L_WBA_SMPS.2, U_WBA.B11
WBA_VLX: L_WBA_SMPS.1, U_WBA.C12
WBA_WAKE: RHOLD2_G.1, U_WBA.F5
YAGI_WILK_A: R_WILK_ISO.1, TP_WILK_A.1
YAGI_WILK_B: R_WILK_ISO.2, TP_WILK_B.1
